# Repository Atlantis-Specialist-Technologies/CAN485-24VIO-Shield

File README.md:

SparkFun AST-CAN485 I/O Shield (24V)
========================================

[*SparkFun AST-CAN485 I/O Shield (24V) (14598)*](https://www.sparkfun.com/products/14598)

The SparkFun AST-CAN485 I/O Shield allows you to use the [AST-CAN485 Dev Board](https://www.sparkfun.com/products/14483) with 24VDC Inputs and Outputs, a popular voltage level for industrial automation devices as well as 5v devices. By providing screw terminals, the board can easily and safely interface with I/O in a semi-permanent manner which allows for inputs, outputs, or the board itself to be swapped out. With all pins pre-populated with either females pin headers or screw terminals, setup time is minimized.

The AST-CAN485 I/O Shield provides a socket to break out all of the I/O of the AST-CAN485 Dev Board. To make a secure connection to your industrial equipment, screw terminals come pre-soldered to the board to get you up and running in no time. The AST-CAN485 I/O Shield is designed to work in the industrial 24V environment, but has a wide supply input range of 7-24V. The board comes with input reverse voltage protection with a green and red status LEDs (green means power is connected properly, and red indicates reversed power, and blocks power to the rest of the board.

Repository Contents
-------------------

* **/Documentation** - Data sheets, additional product information
* **/Hardware** - Eagle design files (.brd, .sch)
* **/Libraries** - Libraries for use with the SparkFun AST-CAN485 I/O Shield (24V)

Documentation
--------------
* **[Library](https://github.com/Atlantis-Specialist-Technologies/AST_V24IO_Arduino_Library)** - Arduino library for the SparkFun AST-CAN485 I/O Shield (24V).
* **[Hookup Guide](https://learn.sparkfun.com/tutorials/ast-can485-io-shield-24v-hookup-guide)** - Basic hookup guide for the SparkFun AST-CAN485 I/O Shield (24V).
* **[SparkFun Fritzing repo](https://github.com/sparkfun/Fritzing_Parts)** - Fritzing diagrams for SparkFun products.

License Information
-------------------

This product is _**open source**_!

Please review the LICENSE.md file for license information.

If you have any questions or concerns on licensing, please contact techsupport@sparkfun.com.

Distributed as-is; no warranty is given.

- Your friends at SparkFun, in collaboration with Atlantis Specialist Technologies

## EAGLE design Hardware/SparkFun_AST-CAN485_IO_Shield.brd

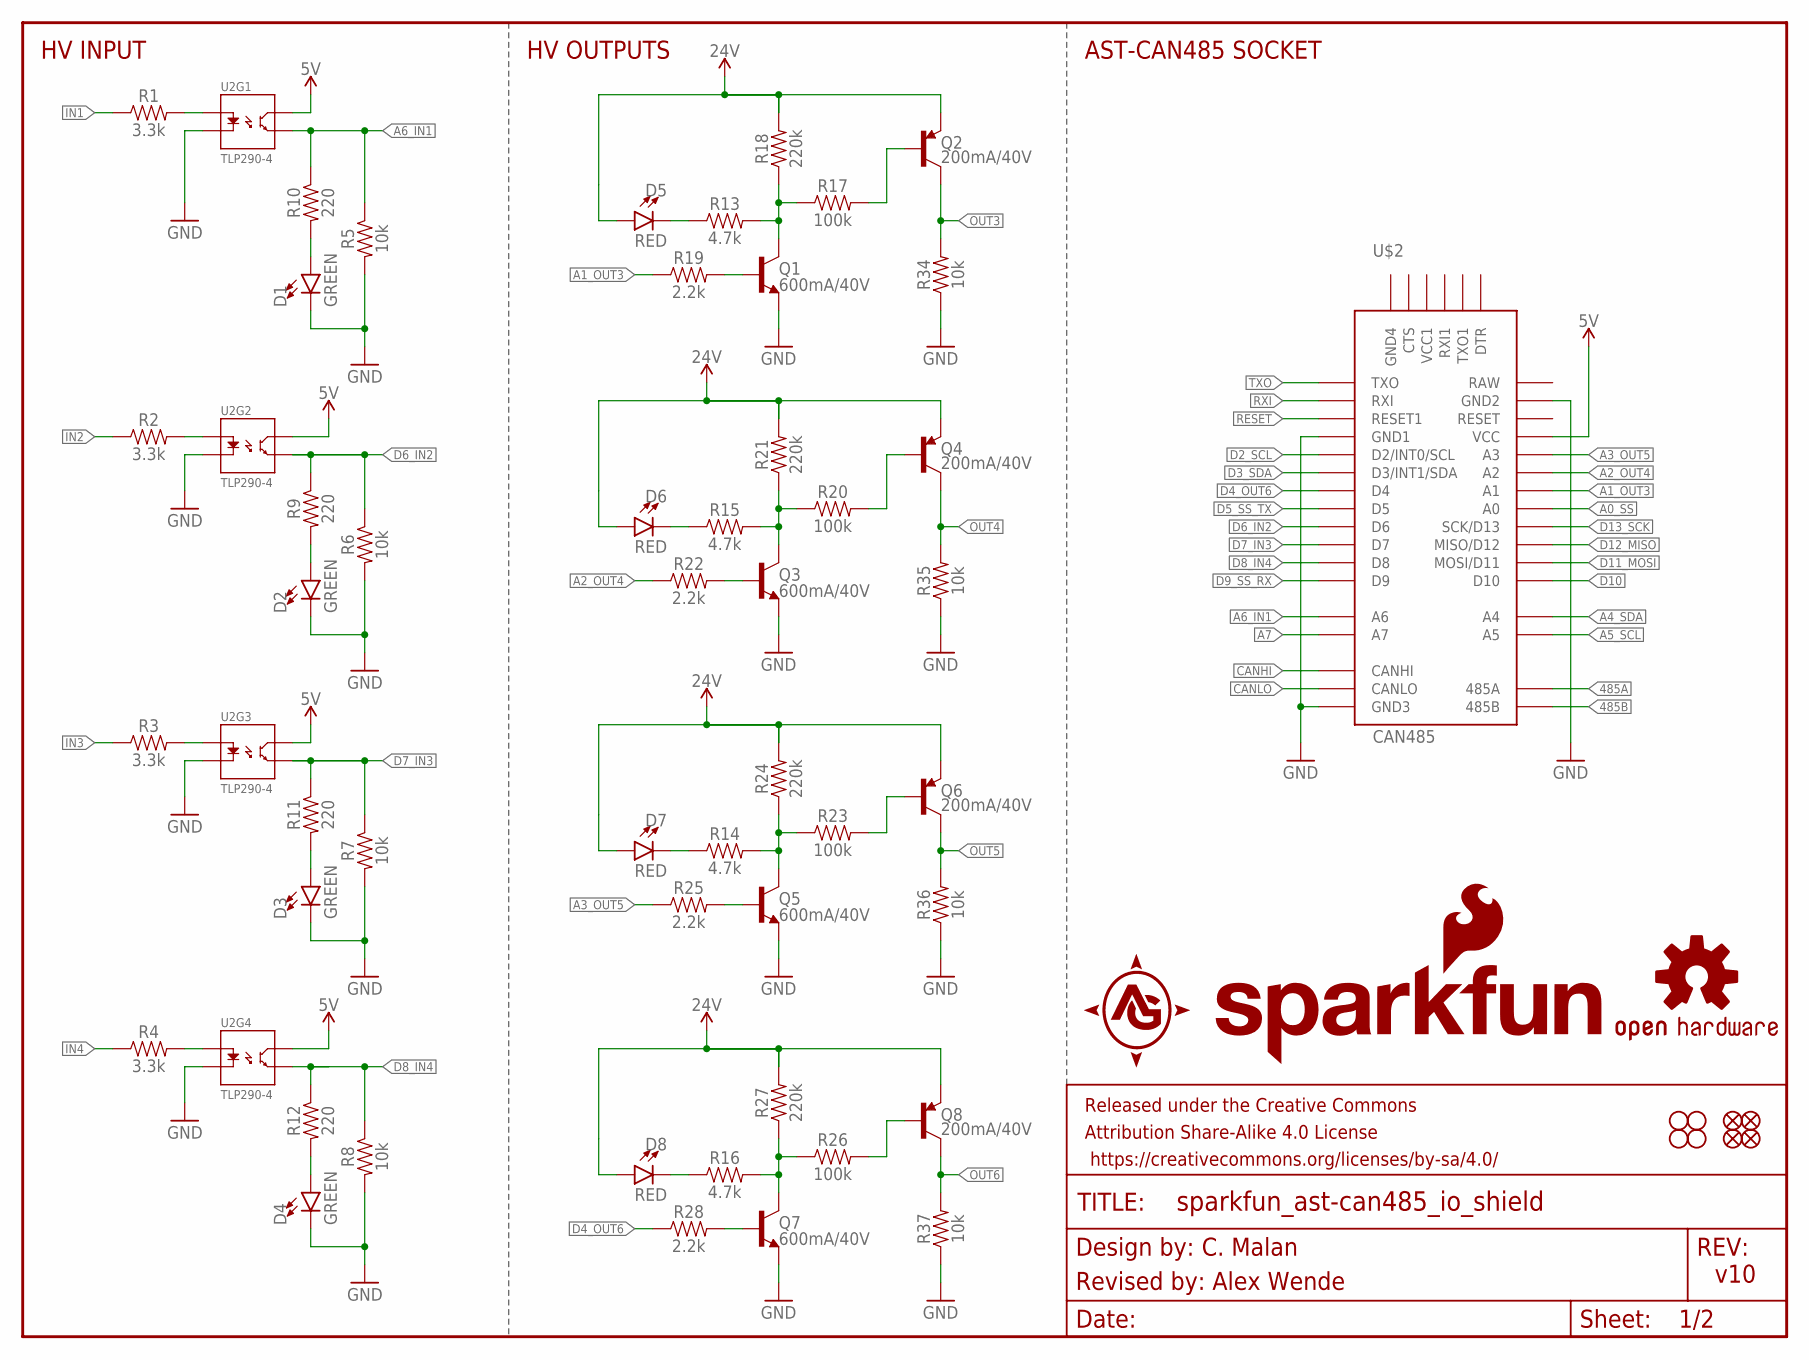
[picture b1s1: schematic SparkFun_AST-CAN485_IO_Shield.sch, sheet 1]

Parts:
D1, D2, D3, D4: GREEN; LED-0603
D5, D6, D7, D8: RED; LED-0603
FD1, FD2, FD3, FD4: FIDUCIALUFIDUCIAL; FIDUCIAL-MICRO
FRAME3: FRAME-LETTER; CREATIVE_COMMONS
H1, H2, H3, H4: STAND-OFF
LOGO1: OSHW-LOGOM; OSHW-LOGO-M
LOGO2: SFE_LOGO_NAME_FLAME.2_INCH; SFE_LOGO_NAME_FLAME_.2
Q1, Q3, Q5, Q7: 600mA/40V; SOT23-3
Q2, Q4, Q6, Q8: 200mA/40V; SOT23-3
R1, R2, R3, R4: 3.3k; 0603
R5, R6, R7, R8, R34, R35, R36, R37: 10k; 0603
R9, R10, R11, R12: 220; 0603
R13, R14, R15, R16: 4.7k; 0603
R17, R20, R23, R26: 100k; 0603
R18, R21, R24, R27: 220k; 0603
R19, R22, R25, R28: 2.2k; 0603
U2: TLP290-4; SO16
U$2: CAN485

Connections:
5V: U2.10 (CL1), U2.12 (CL1), U2.14 (CL1), U2.16 (CL1), U$2.VCC; also elsewhere on the board
24V: D5.A, D6.A, D7.A, D8.A, Q2.2 (E), Q4.2 (E), Q6.2 (E), Q8.2 (E), R18.2, R21.2, R24.2, R27.2; also elsewhere on the board
485A: U$2.485A; also elsewhere on the board
485B: U$2.485B; also elsewhere on the board
A0_SS: U$2.A0; also elsewhere on the board
A1_OUT3: R19.1, U$2.A1; also elsewhere on the board
A2_OUT4: R22.1, U$2.A2; also elsewhere on the board
A3_OUT5: R25.1, U$2.A3; also elsewhere on the board
A4_SDA: U$2.A4; also elsewhere on the board
A5_SCL: U$2.A5; also elsewhere on the board
A6_IN1: R5.1, R10.1, U2.15 (EM1), U$2.A6; also elsewhere on the board
A7: U$2.A7; also elsewhere on the board
CANHI: U$2.CANHI; also elsewhere on the board
CANLO: U$2.CANLO; also elsewhere on the board
D2_SCL: U$2.2 (D2/INT0/SCL); also elsewhere on the board
D3_SDA: U$2.3 (D3/INT1/SDA); also elsewhere on the board
D4_OUT6: R28.1, U$2.4 (D4); also elsewhere on the board
D5_SS_TX: U$2.5 (D5); also elsewhere on the board
D6_IN2: R6.1, R9.1, U2.13 (EM1), U$2.6 (D6); also elsewhere on the board
D7_IN3: R7.1, R11.1, U2.11 (EM1), U$2.7 (D7); also elsewhere on the board
D8_IN4: R8.1, R12.1, U2.9 (EM1), U$2.8 (D8); also elsewhere on the board
D9_SS_RX: U$2.9 (D9); also elsewhere on the board
D10: U$2.10 (D10); also elsewhere on the board
D11_MOSI: U$2.11 (MOSI/D11); also elsewhere on the board
D12_MISO: U$2.12 (MISO/D12); also elsewhere on the board
D13_SCK: U$2.13 (SCK/D13); also elsewhere on the board
GND: D1.C, D2.C, D3.C, D4.C, Q1.2 (E), Q3.2 (E), Q5.2 (E), Q7.2 (E), R5.2, R6.2, R7.2, R8.2, R34.1, R35.1, R36.1, R37.1, U2.2 (C1), U2.4 (C1), U2.6 (C1), U2.8 (C1), U$2.GND1, U$2.GND2, U$2.GND3; also elsewhere on the board
IN1: R1.1; also elsewhere on the board
IN2: R2.1; also elsewhere on the board
IN3: R3.1; also elsewhere on the board
IN4: R4.1; also elsewhere on the board
unnamed: R1.2, U2.1 (A1)
unnamed: R3.2, U2.5 (A1)
unnamed: R4.2, U2.7 (A1)
unnamed: R2.2, U2.3 (A1)
unnamed: Q2.1 (B), R17.2
unnamed: Q1.3 (C), R13.2, R17.1, R18.1
unnamed: Q1.1 (B), R19.2
unnamed: Q4.1 (B), R20.2
unnamed: Q3.3 (C), R15.2, R20.1, R21.1
unnamed: D2.A, R9.2
unnamed: Q3.1 (B), R22.2
unnamed: Q6.1 (B), R23.2
unnamed: Q5.3 (C), R14.2, R23.1, R24.1
unnamed: Q5.1 (B), R25.2
unnamed: Q8.1 (B), R26.2
unnamed: Q7.3 (C), R16.2, R26.1, R27.1
unnamed: Q7.1 (B), R28.2
unnamed: D1.A, R10.2
unnamed: D4.A, R12.2
unnamed: D3.A, R11.2
unnamed: D5.C, R13.1
unnamed: D7.C, R14.1
unnamed: D6.C, R15.1
unnamed: D8.C, R16.1
OUT3: Q2.3 (C), R34.2; also elsewhere on the board
OUT4: Q4.3 (C), R35.2; also elsewhere on the board
OUT5: Q6.3 (C), R36.2; also elsewhere on the board
OUT6: Q8.3 (C), R37.2; also elsewhere on the board
RESET: U$2.RST1 (RESET1); also elsewhere on the board
RXI: U$2.RXI; also elsewhere on the board
TXO: U$2.TXO; also elsewhere on the board

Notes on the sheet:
HV INPUT
HV OUTPUTS
AST-CAN485 SOCKET
C. Malan
Revised by: Alex Wende
v10

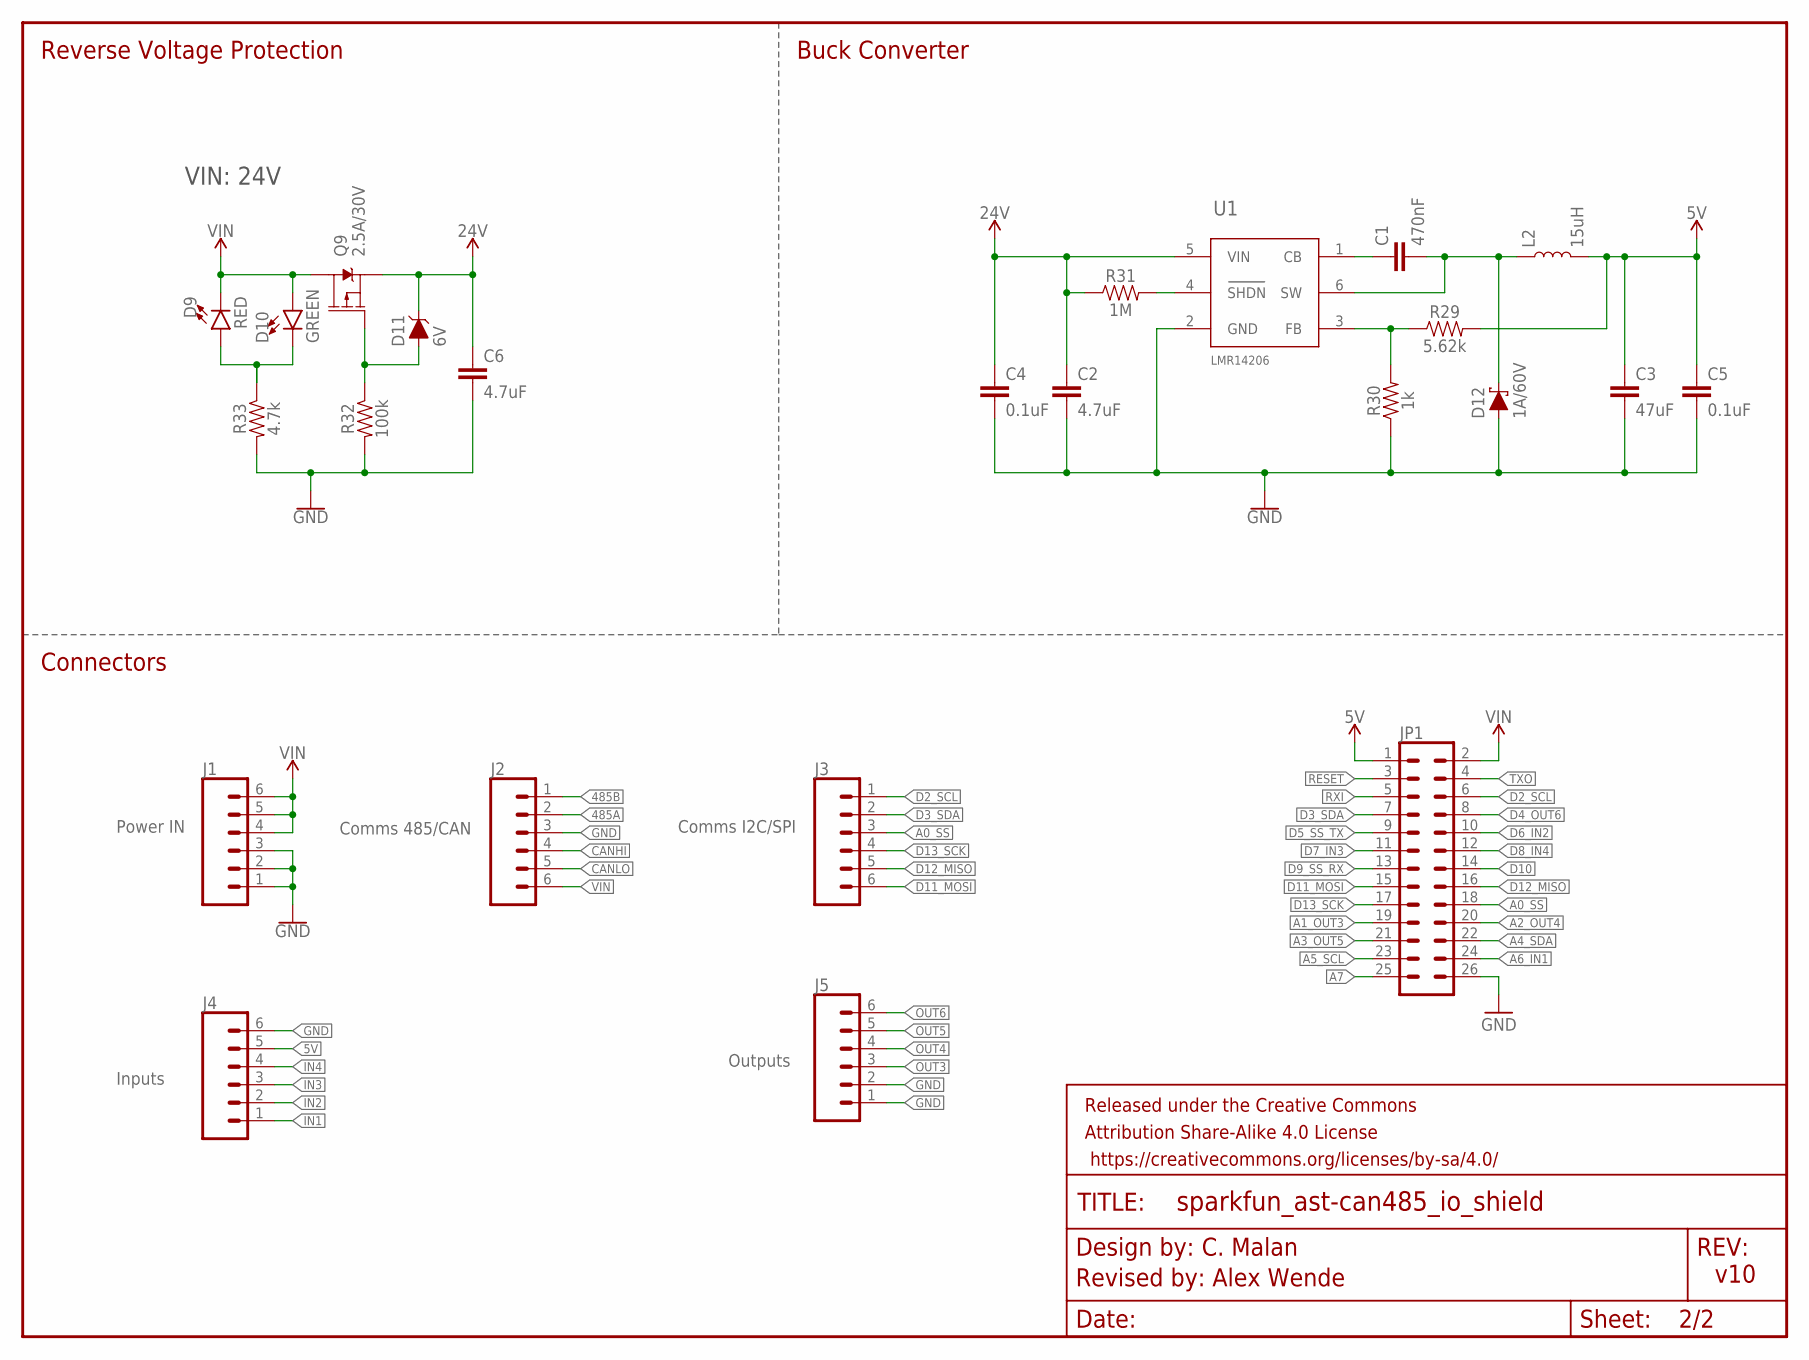
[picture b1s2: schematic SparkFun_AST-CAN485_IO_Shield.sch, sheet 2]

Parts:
C1: 470nF; 0603
C2, C6: 4.7uF; 0603
C3: 47uF; 0805
C4, C5: 0.1uF; 0603
D9: RED; LED-0603
D10: GREEN; LED-0603
D11: 6V; SOT23-3
D12: 1A/60V; DIODE-MICRO-SMP
FRAME1: FRAME-LETTERNO_PACKAGE; DUMMY
J1, J2, J3, J4, J5: CONN_063.5MM-6; SCREWTERMINAL-3.5MM-6
JP1: CONN_13X22X13; 2X13
L2: 15uH; INDUCTOR_LQH32
Q9: 2.5A/30V; SOT23-3
R29: 5.62k; 0603
R30: 1k; 0603
R31: 1M; 0603
R32: 100k; 0603
R33: 4.7k; 0603
U1: LMR14206; SOT23-6

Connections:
5V: C3.1, C5.1, J4.5, JP1.1, L2.P$2 (2), R29.2; also elsewhere on the board
24V: C2.1, C4.1, C6.1, D11.3 (C), Q9.2 (S), R31.1, U1.5 (VIN); also elsewhere on the board
485A: J2.2; also elsewhere on the board
485B: J2.1; also elsewhere on the board
A0_SS: J3.3, JP1.18; also elsewhere on the board
A1_OUT3: JP1.19; also elsewhere on the board
A2_OUT4: JP1.20; also elsewhere on the board
A3_OUT5: JP1.21; also elsewhere on the board
A4_SDA: JP1.22; also elsewhere on the board
A5_SCL: JP1.23; also elsewhere on the board
A6_IN1: JP1.24; also elsewhere on the board
A7: JP1.25; also elsewhere on the board
CANHI: J2.4; also elsewhere on the board
CANLO: J2.5; also elsewhere on the board
D2_SCL: J3.1, JP1.6; also elsewhere on the board
D3_SDA: J3.2, JP1.7; also elsewhere on the board
D4_OUT6: JP1.8; also elsewhere on the board
D5_SS_TX: JP1.9; also elsewhere on the board
D6_IN2: JP1.10; also elsewhere on the board
D7_IN3: JP1.11; also elsewhere on the board
D8_IN4: JP1.12; also elsewhere on the board
D9_SS_RX: JP1.13; also elsewhere on the board
D10: JP1.14; also elsewhere on the board
D11_MOSI: J3.6, JP1.15; also elsewhere on the board
D12_MISO: J3.5, JP1.16; also elsewhere on the board
D13_SCK: J3.4, JP1.17; also elsewhere on the board
FB: R29.1, R30.2, U1.3 (FB)
GND: C2.2, C3.2, C4.2, C5.2, C6.2, D12.A, J1.1, J1.2, J1.3, J2.3, J4.6, J5.1, J5.2, JP1.26, R30.1, R32.2, R33.2, U1.2 (GND); also elsewhere on the board
IN1: J4.1; also elsewhere on the board
IN2: J4.2; also elsewhere on the board
IN3: J4.3; also elsewhere on the board
IN4: J4.4; also elsewhere on the board
unnamed: D9.A, D10.C, R33.1
unnamed: D11.1 (A), Q9.1 (G), R32.1
OUT3: J5.3; also elsewhere on the board
OUT4: J5.4; also elsewhere on the board
OUT5: J5.5; also elsewhere on the board
OUT6: J5.6; also elsewhere on the board
RESET: JP1.3; also elsewhere on the board
RXI: JP1.5; also elsewhere on the board
SHDN: R31.2, U1.4 (SHDN)
TXO: JP1.4; also elsewhere on the board
VBOOT: C1.1, U1.1 (CB)
VIN: D9.C, D10.A, J1.4, J1.5, J1.6, J2.6, JP1.2, Q9.3 (D)
VSW: C1.2, D12.C, L2.P$1 (1), U1.6 (SW)

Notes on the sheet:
Power IN
Comms 485/CAN
Comms I2C/SPI
Inputs
Outputs
Reverse Voltage Protection
Buck Converter
Connectors
v10
C. Malan
Revised by: Alex Wende
VIN: 24V

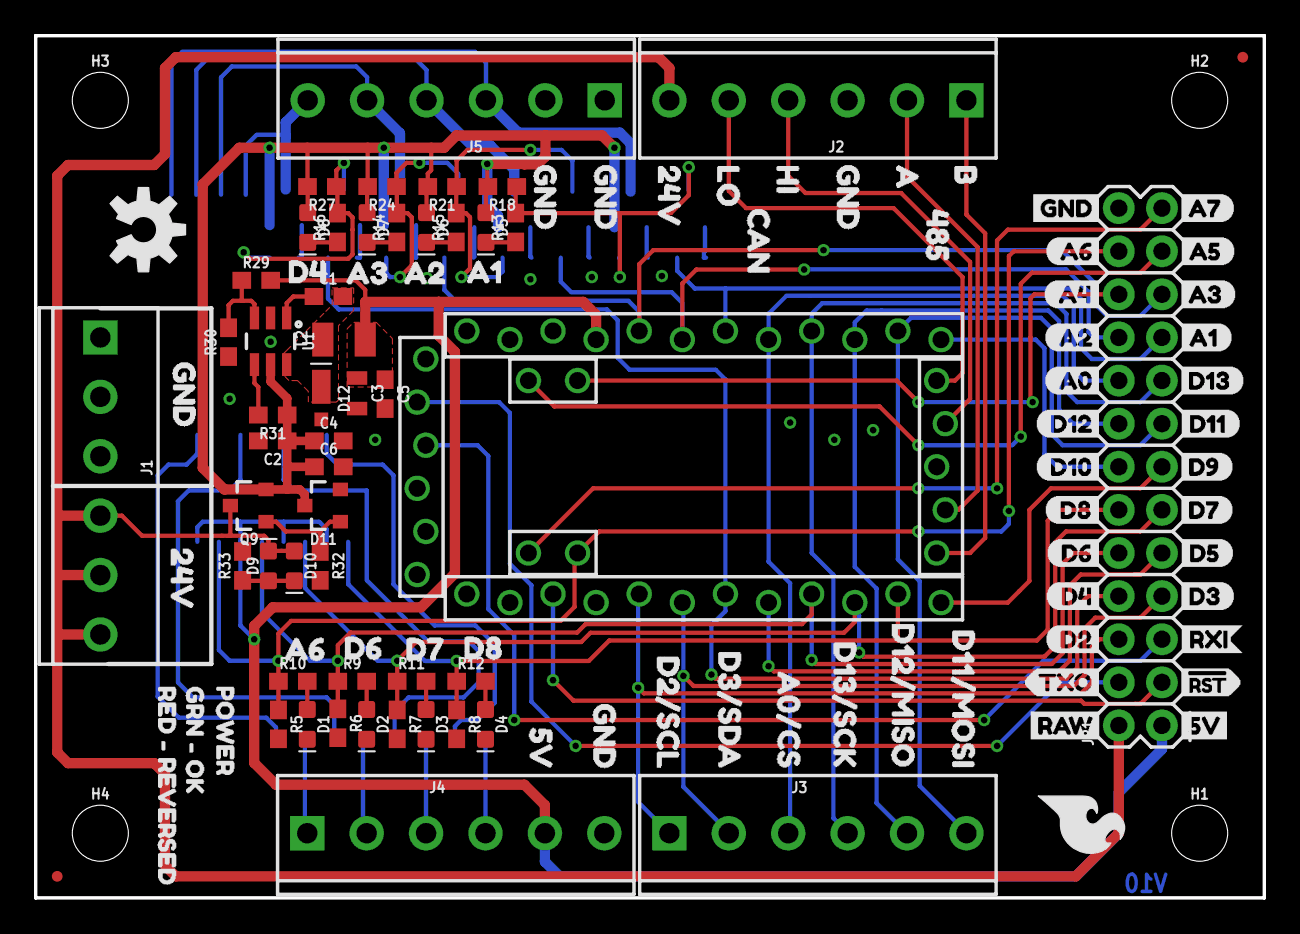
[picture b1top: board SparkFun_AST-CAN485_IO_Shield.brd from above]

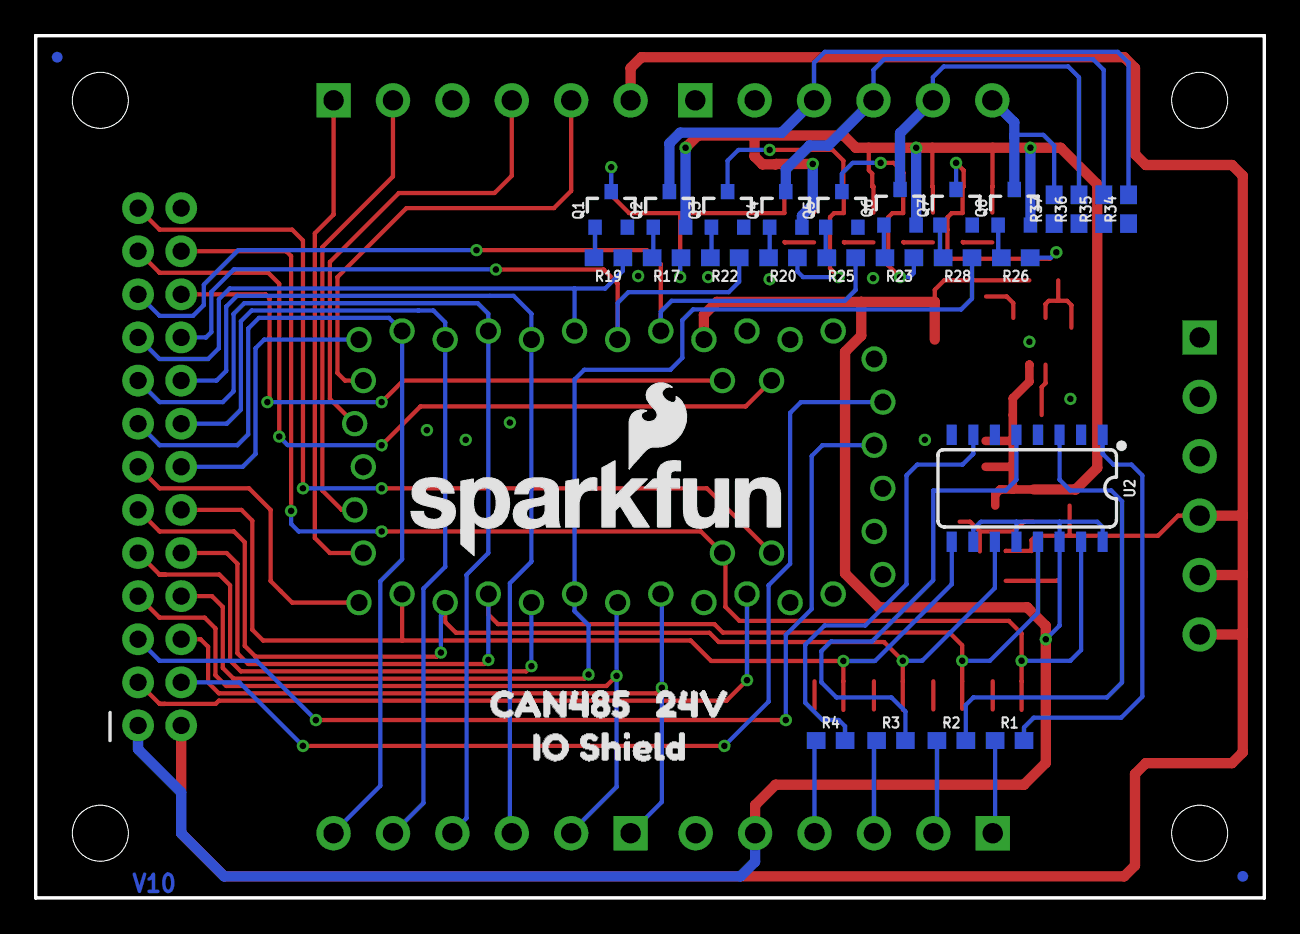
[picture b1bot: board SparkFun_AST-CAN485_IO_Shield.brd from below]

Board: 2 copper layers, 72.4 x 50.8 mm, 147 parts (31 on the bottom side), 69 nets.

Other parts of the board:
U$1: #RST27
U$3: 5V26
U$4: A60
U$5: D319
U$6: D517
U$7: D715
U$8: D913
U$9: D1111
U$10: D139
U$11: A17
U$12: A35
U$13: A53
U$14: A71
U$15, U$29, U$44, U$45, U$49, U$55: GND0
U$16: RAW25
U$17: RXI10
U$18: A41
U$19: A22
U$20: A03
U$21: D124
U$22: D105
U$23: D86
U$24: D67
U$25: D48
U$26: D29
U$27: TXO11
U$28: 5V19
U$30: D818
U$31: D717
U$32: D616
U$33: A615
U$34: D2#SCL20
U$35: D3#SDA21
U$36: A0#CS22
U$37: D13#SCK23
U$38: D12#MISO24
U$39: D11#MOSI25
U$40: D413
U$41: A311
U$42: _A210
U$43: A112
U$46, U$54, U$61: 24V1
U$47: LO2
U$48: HI3
U$50: A6
U$51: B7
U$52: 4858
U$53: CAN4
U$56: RED_#_REVERSED3
U$57: GRN_#_OK1
U$58: POWER0
U$59: CAN4850
U$60: SFE_LOGO_FLAME_.2
U$62: IO_SHIELD2

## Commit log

2019-02-14 Readme
2019-02-14 Add readme and hardware
2019-02-14 Upload Pinout
2019-02-14 Update Readme
    Updated with placeholder images
2019-02-14 License
2019-02-15 Update README.md
    Updating with SparkFun formatted links and text

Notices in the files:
parts and their libraries:
SparkFun-Aesthetics: Licensing: Creative Commons ShareAlike 4.0 International - https://creativecommons.org/licenses/by-sa/4.0
SparkFun-Aesthetics: Released under the Creative Commons Attribution Share-Alike 4.0 License
SparkFun-Aesthetics: https://creativecommons.org/licenses/by-sa/4.0
